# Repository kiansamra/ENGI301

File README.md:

<h1> ENGI301 </h1>
Repository for Engi301 course work

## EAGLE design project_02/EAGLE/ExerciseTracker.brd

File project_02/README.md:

# Exercise Tracker PCB

This repository provides the files for the PCB implementation of the following [Hackster Project](https://www.hackster.io/kiansamra/exercise-tracker-2aaf67).

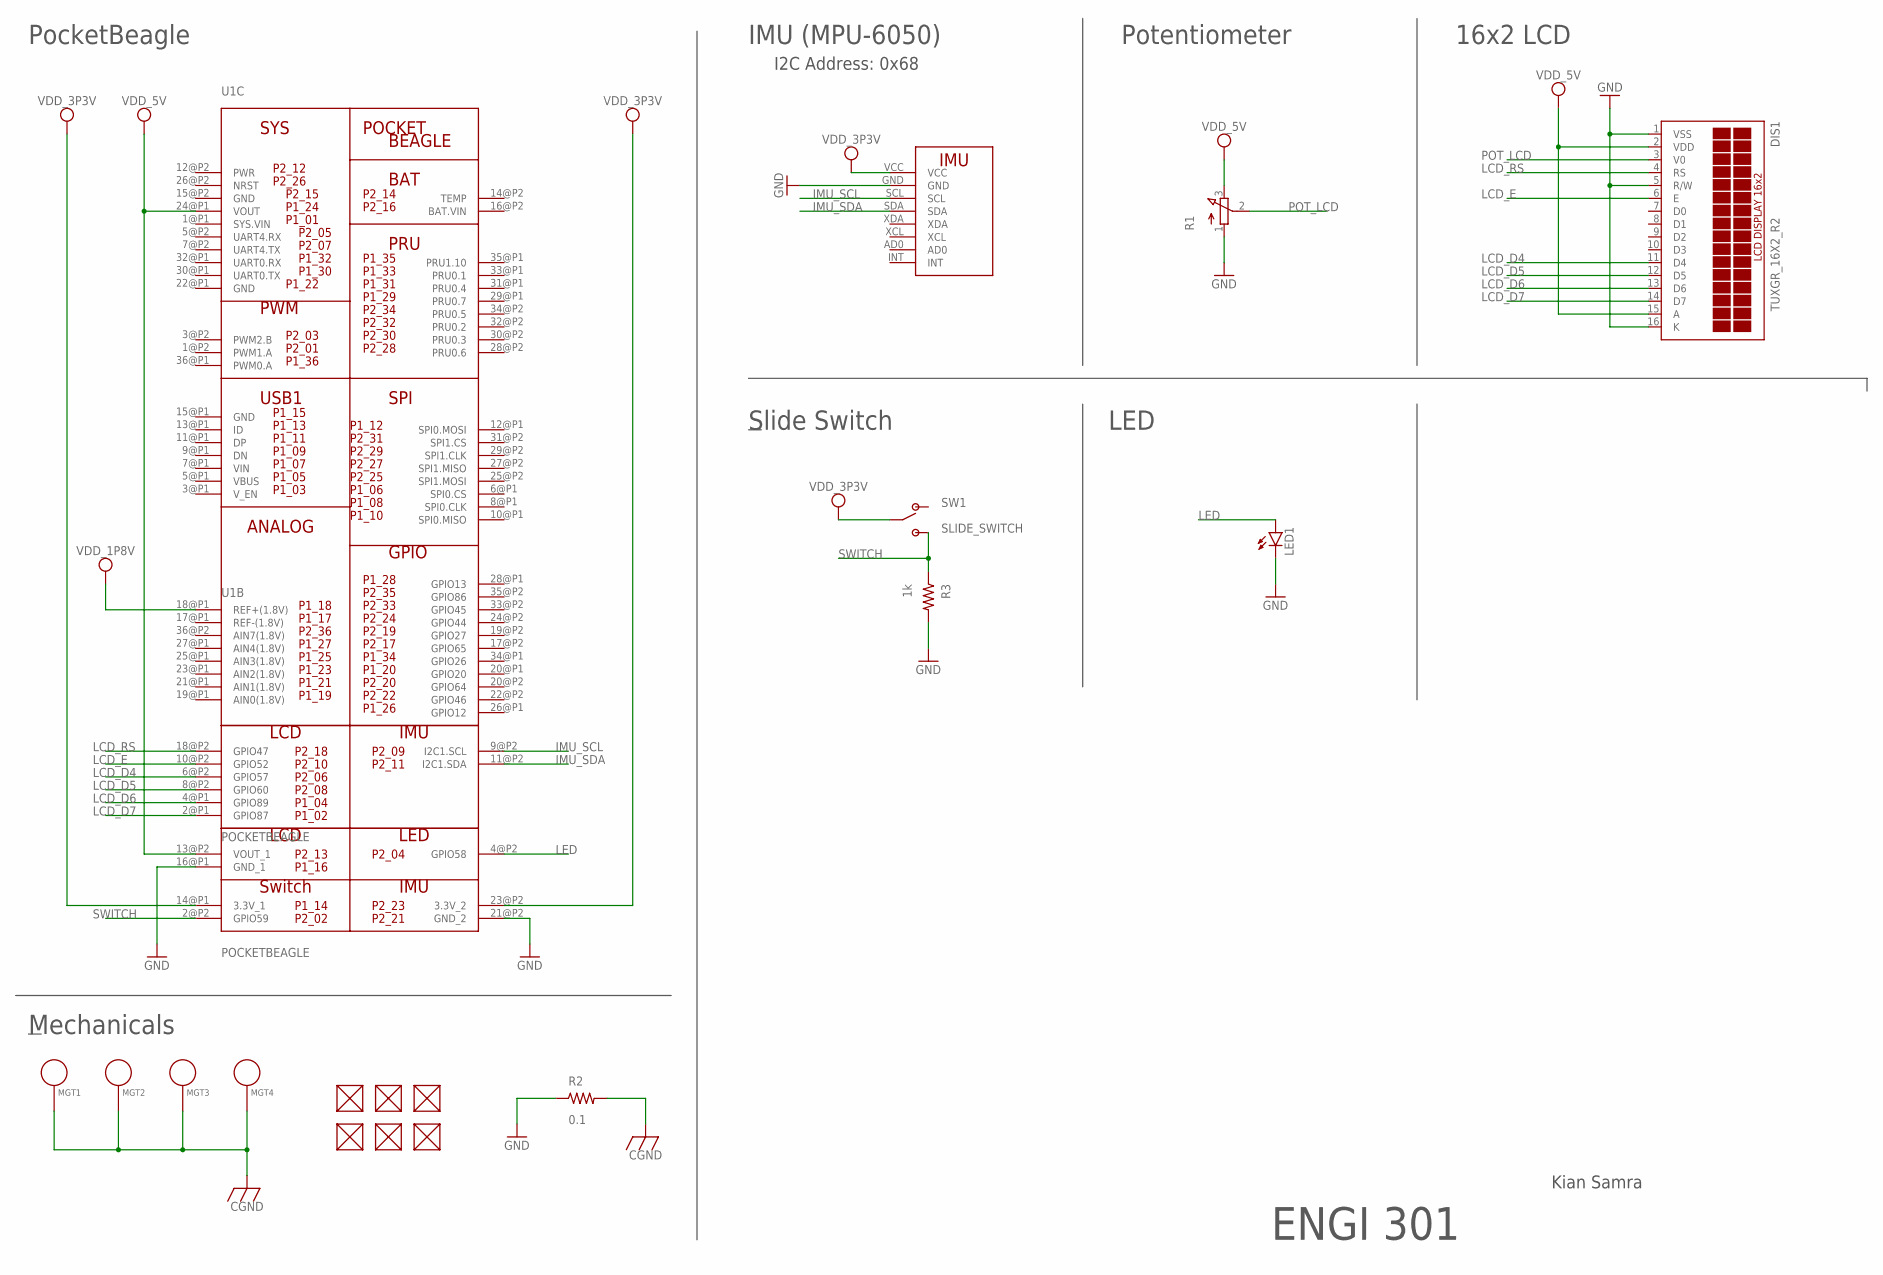
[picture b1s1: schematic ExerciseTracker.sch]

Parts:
DIS1: TUXGR_16X2_R2
FUD2, FUD3, FUD4, FUD5, FUD6, FUD7: FIDUCIAL; FIDUCIAL_40MIL
LED1: LED5MM
MGT1, MGT2, MGT3, MGT4: MOUNTING_HOLE
R1: POTENTIOMETER; 3RP/1610N
R2: 0.1; R0603
R3: 1k; R0603
SW1: SLIDE_SWITCH; JS202011SCQN
U1: POCKETBEAGLE
U$2: MPU6050

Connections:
CGND: MGT1.P$1, MGT2.P$1, MGT3.P$1, MGT4.P$1, R2.2
GND: DIS1.1 (VSS), DIS1.5 (R/W), DIS1.16 (K), LED1.K (C), R1.1 (A), R2.1, R3.2, U1.16@P1 (GND_1), U1.21@P2 (GND_2), U$2.GND
IMU_SCL: U1.9@P2 (I2C1.SCL), U$2.SCL
IMU_SDA: U1.11@P2 (I2C1.SDA), U$2.SDA
LCD_D4: DIS1.11 (D4), U1.6@P2 (GPIO57)
LCD_D5: DIS1.12 (D5), U1.8@P2 (GPIO60)
LCD_D6: DIS1.13 (D6), U1.4@P1 (GPIO89)
LCD_D7: DIS1.14 (D7), U1.2@P1 (GPIO87)
LCD_E: DIS1.6 (E), U1.10@P2 (GPIO52)
LCD_RS: DIS1.4 (RS), U1.18@P2 (GPIO47)
LED: LED1.A, U1.4@P2 (GPIO58)
POT_LCD: DIS1.3 (V0), R1.2 (S)
SWITCH: R3.1, SW1.3 (POS2), SW1.6 (POS2), U1.2@P2 (GPIO59)
VDD_1P8V: U1.18@P1 (REF+(1.8V))
VDD_3P3V: SW1.2 (COMM), SW1.5 (COMM), U1.14@P1 (3.3V_1), U1.23@P2 (3.3V_2), U$2.VCC
VDD_5V: DIS1.2 (VDD), DIS1.15 (A), R1.3 (E), U1.13@P2 (VOUT_1), U1.24@P1 (VOUT)

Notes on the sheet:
PocketBeagle
IMU (MPU-6050)
Potentiometer
16x2 LCD
Slide Switch
LED
I2C Address: 0x68
Mechanicals
Kian Samra
ENGI 301

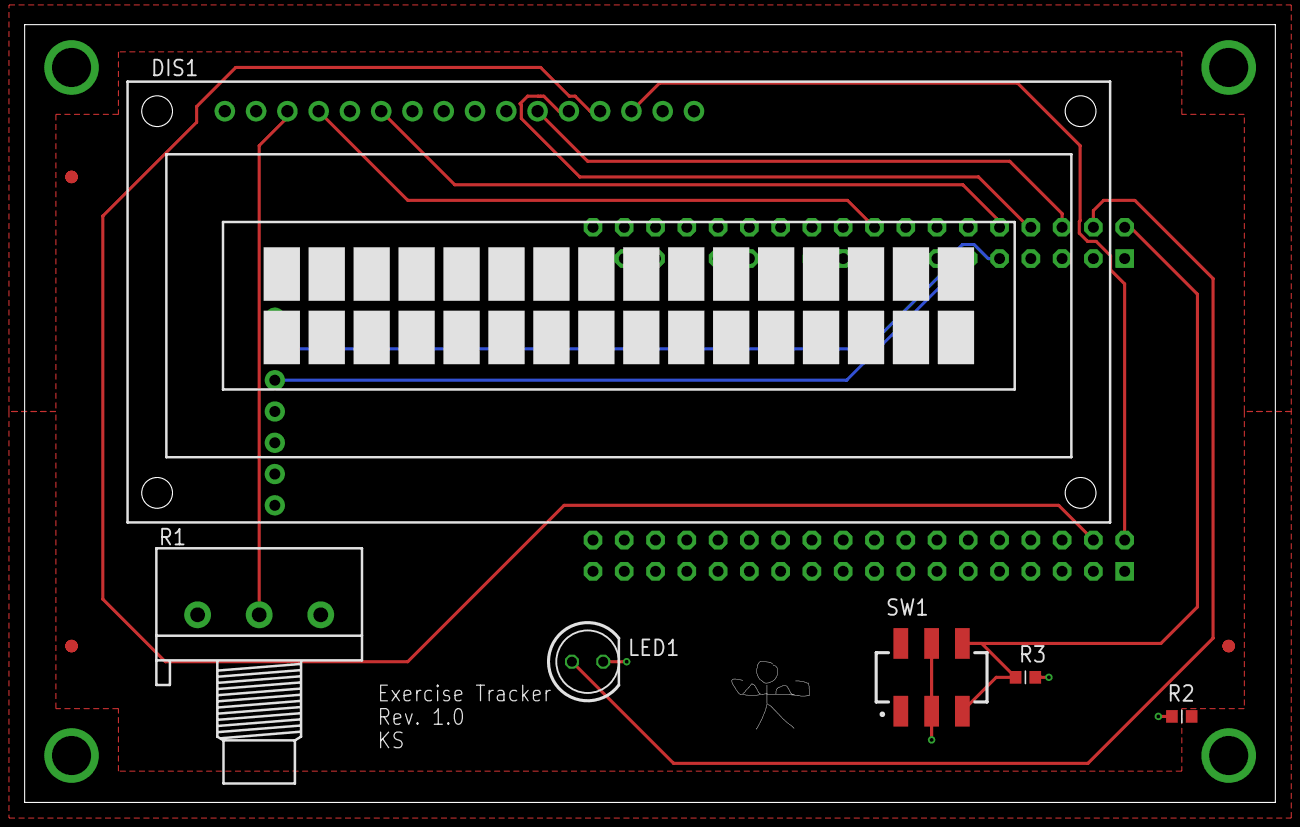
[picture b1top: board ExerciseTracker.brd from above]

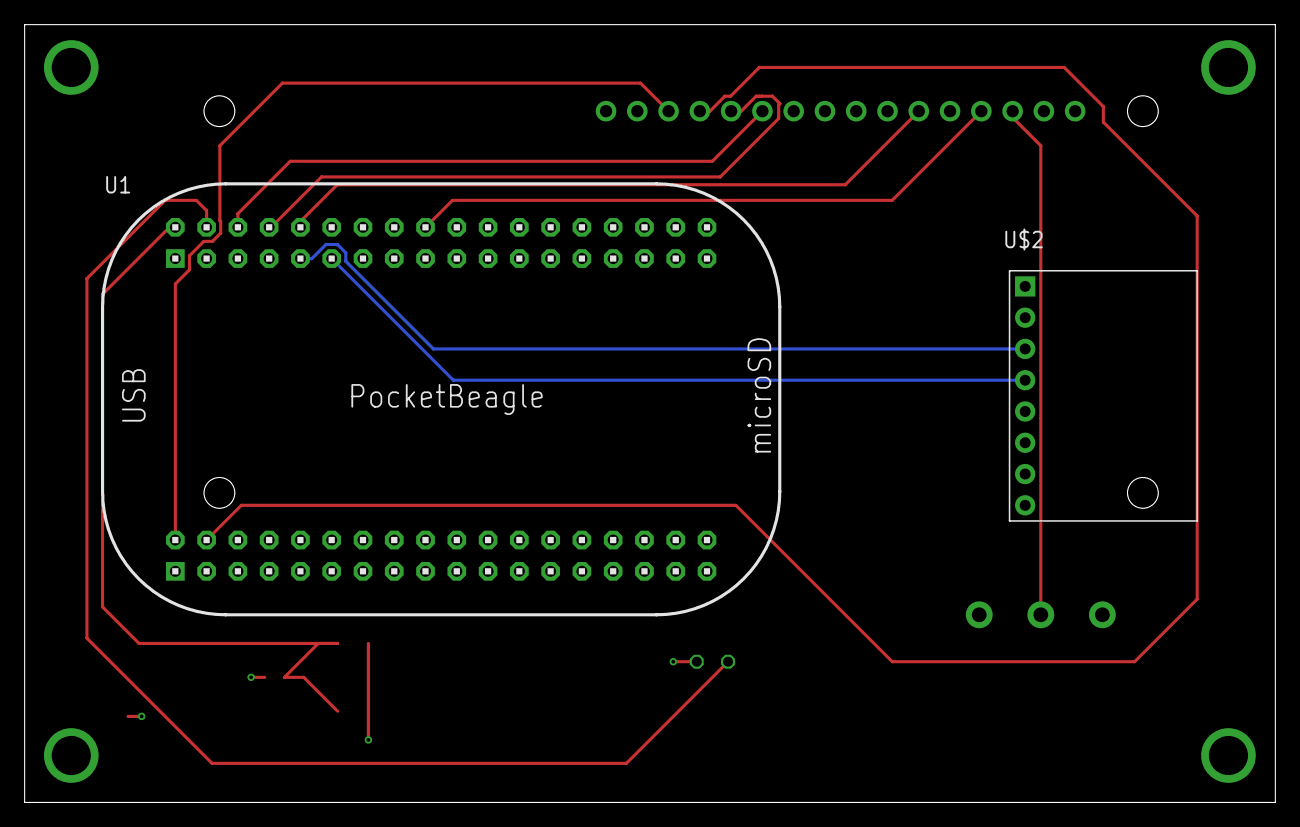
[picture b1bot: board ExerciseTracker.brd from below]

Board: 4 copper layers, 101.6 x 63.2 mm, 18 parts (2 on the bottom side), 15 nets.

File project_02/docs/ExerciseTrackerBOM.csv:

"Qty;""Value"";""Device"";""Package"";""Parts"";""Description"";""MF"";""MPN"";""OC_FARNELL"";""OC_NEWARK"";""POPULARITY"";",
"1;"""";""LED5MM"";""LED5MM"";""LED1"";""LED"";"""";"""";"""";"""";""93"";",
"1;"""";""POTENTIOMETER"";""3RP/1610N"";""R1"";""16mm Potentiometer one level"";"""";"""";"""";"""";""8"";",
"1;""0.1"";""R_R0603"";""R0603"";""R2"";""RESISTOR"," American symbol"";"""";"""";"""";"""";"""";"
"1;""1k"";""R_R0603"";""R0603"";""R3"";""RESISTOR"," American symbol"";"""";"""";"""";"""";"""";"
"1;""MPU6050"";""MPU6050"";""MPU6050"";""U$2"";"""";"""";"""";"""";"""";"""";",
"1;""POCKETBEAGLE"";""POCKETBEAGLE"";""POCKETBEAGLE"";""U1"";"""";"""";"""";"""";"""";"""";",
"1;""SLIDE_SWITCH"";""SLIDE_SWITCH"";""JS202011SCQN"";""SW1"";""JS202011SCQN SPDT Slide Switch"";"""";"""";"""";"""";"""";",
"1;""TUXGR_16X2_R2"";""TUXGR_16X2_R2"";""TUXGR_16X2_R2"";""DIS1"";""Tuxgraphics LCD display 16x2 characters reflective"," without background light"";"""";"""";""unknown"";""unknown"";""5"";"

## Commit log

2023-09-11 Updating README.md
2023-11-08 software
